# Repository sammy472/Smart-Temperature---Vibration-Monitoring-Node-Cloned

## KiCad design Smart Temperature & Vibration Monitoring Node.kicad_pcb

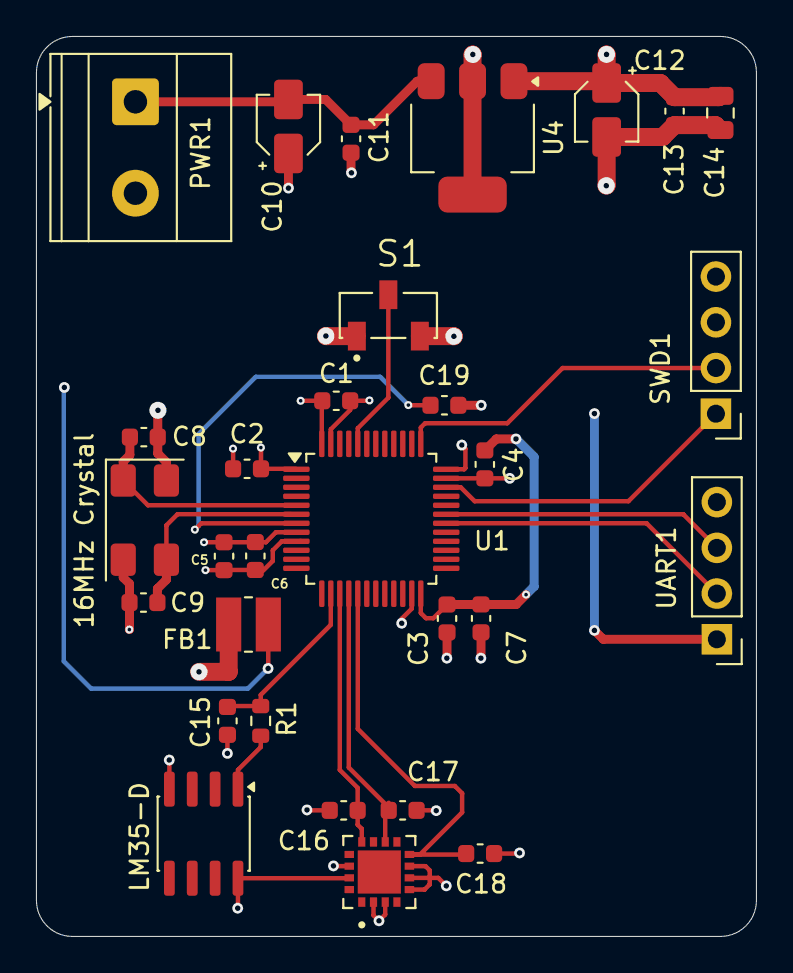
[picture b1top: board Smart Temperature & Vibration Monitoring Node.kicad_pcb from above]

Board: 4 copper layers, 40.0 x 50.0 mm, 30 parts (0 on the bottom side), 17 nets.

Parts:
16MHz Crystal: 16 MHz; Crystal_SMD_0603-4Pin_6.0x3.5mm
C1, C2, C3, C4, C6, C7, C8, C9, C15, C19: 100nF; C_0603_1608Metric
C5: 10nF; C_0603_1608Metric
C10, C12: 10uF; CP_Elec_3x5.4
C11, C13, C16, C17, C18: 0.1uF; C_0603_1608Metric
C14: 10uF; C_0805_2012Metric
FB1: L_Ferrocore_DLG-0302
LM35-D: LM35-D; SOIC-8_3.9x4.9mm_P1.27mm
PWR1: Conn_01x02_Pin; TerminalBlock_Phoenix_MKDS-1,5-2-5.08_1x02_P5.08mm_Horizont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
R1: 100; R_0603_1608Metric
S1: CJS-1200TA; SW_CJS-1200TA
SWD1: Conn_01x04_Pin; PinHeader_1x04_P2.54mm_Vertical
U1: STM32F103C8Tx; LQFP-48_7x7mm_P0.5mm
U4: AMS1117-3.3; SOT-223-3_TabPin2
U5: ADXL335BCPZ-RL; PQFN65P400X400X150-17N
UART1: Conn_01x04_Pin; PinHeader_1x04_P2.54mm_Vertical

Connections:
+3.3V: C1.2, C2.2, C3.2, C4.2, C7.2, C12.2, C13.2, C14.1, FB1.2, S1.1, SWD1.3, U1.1 (VBAT), U1.24 (VDD), U1.36 (VDD), U1.48 (VDD), U4.2 (VO), UART1.1
+3.3VA: C5.2, C6.2, FB1.1, LM35-D.8 (+V_{S}), U1.9 (VDDA), U5.14 (VS), U5.15 (VS)
/ADC_LM35: C15.2, R1.2, U1.14 (PA4)
/BOOT0: S1.2, U1.44 (BOOT0)
/HSE_IN: 16MHz Crystal.1, C8.2, U1.5 (PD0)
/HSE_OUT: 16MHz Crystal.3, C9.2, U1.6 (PD1)
/NRST: C19.2, U1.7 (NRST)
/RX: U1.31 (PA10), UART1.3
/SWCLK: SWD1.2, U1.37 (PA14)
/SWDIO: SWD1.1, U1.34 (PA13)
/TX: U1.30 (PA9), UART1.2
/Xout: C16.2, U1.15 (PA5), U5.12 (XOUT)
/Yout: C17.2, U1.16 (PA6), U5.10 (YOUT)
/Zout: C18.2, U1.17 (PA7), U5.8 (ZOUT)
GND: 16MHz Crystal.2 (G), 16MHz Crystal.4 (G), C1.1, C2.1, C3.1, C4.1, C5.1, C6.1, C7.1, C8.1, C9.1, C10.1, C11.1, C12.1, C13.1, C14.2, C15.1, C16.1, C17.1, C18.1, C19.1, LM35-D.4 (GND), PWR1.2, S1.3, SWD1.4, U1.8 (VSSA), U1.23 (VSS), U1.35 (VSS), U1.47 (VSS), U4.1 (GND), U5.2 (ST), U5.3 (COM), U5.5 (COM), U5.6 (COM), U5.7 (COM), UART1.4
unnamed: LM35-D.1 (V_{OUT}), R1.1
unnamed: C10.2, C11.2, PWR1.1, U4.3 (VI)
